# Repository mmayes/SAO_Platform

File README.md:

# SAP Display Platform

I had made this project after returning home from Def Con 30 with a brand 
new colelction of SAOs that jsut had to be displayed somehow.

## Fabrication

I had targeted JLCPCB.com as the manufacturer of this pcb to include their 
pick and place service. To that end the zipped gerber file along with 
the files contained within the fabrication folder were sufficient to 
facilaite that. It's quite possible that the LCSC Part number may have 
changed since then.

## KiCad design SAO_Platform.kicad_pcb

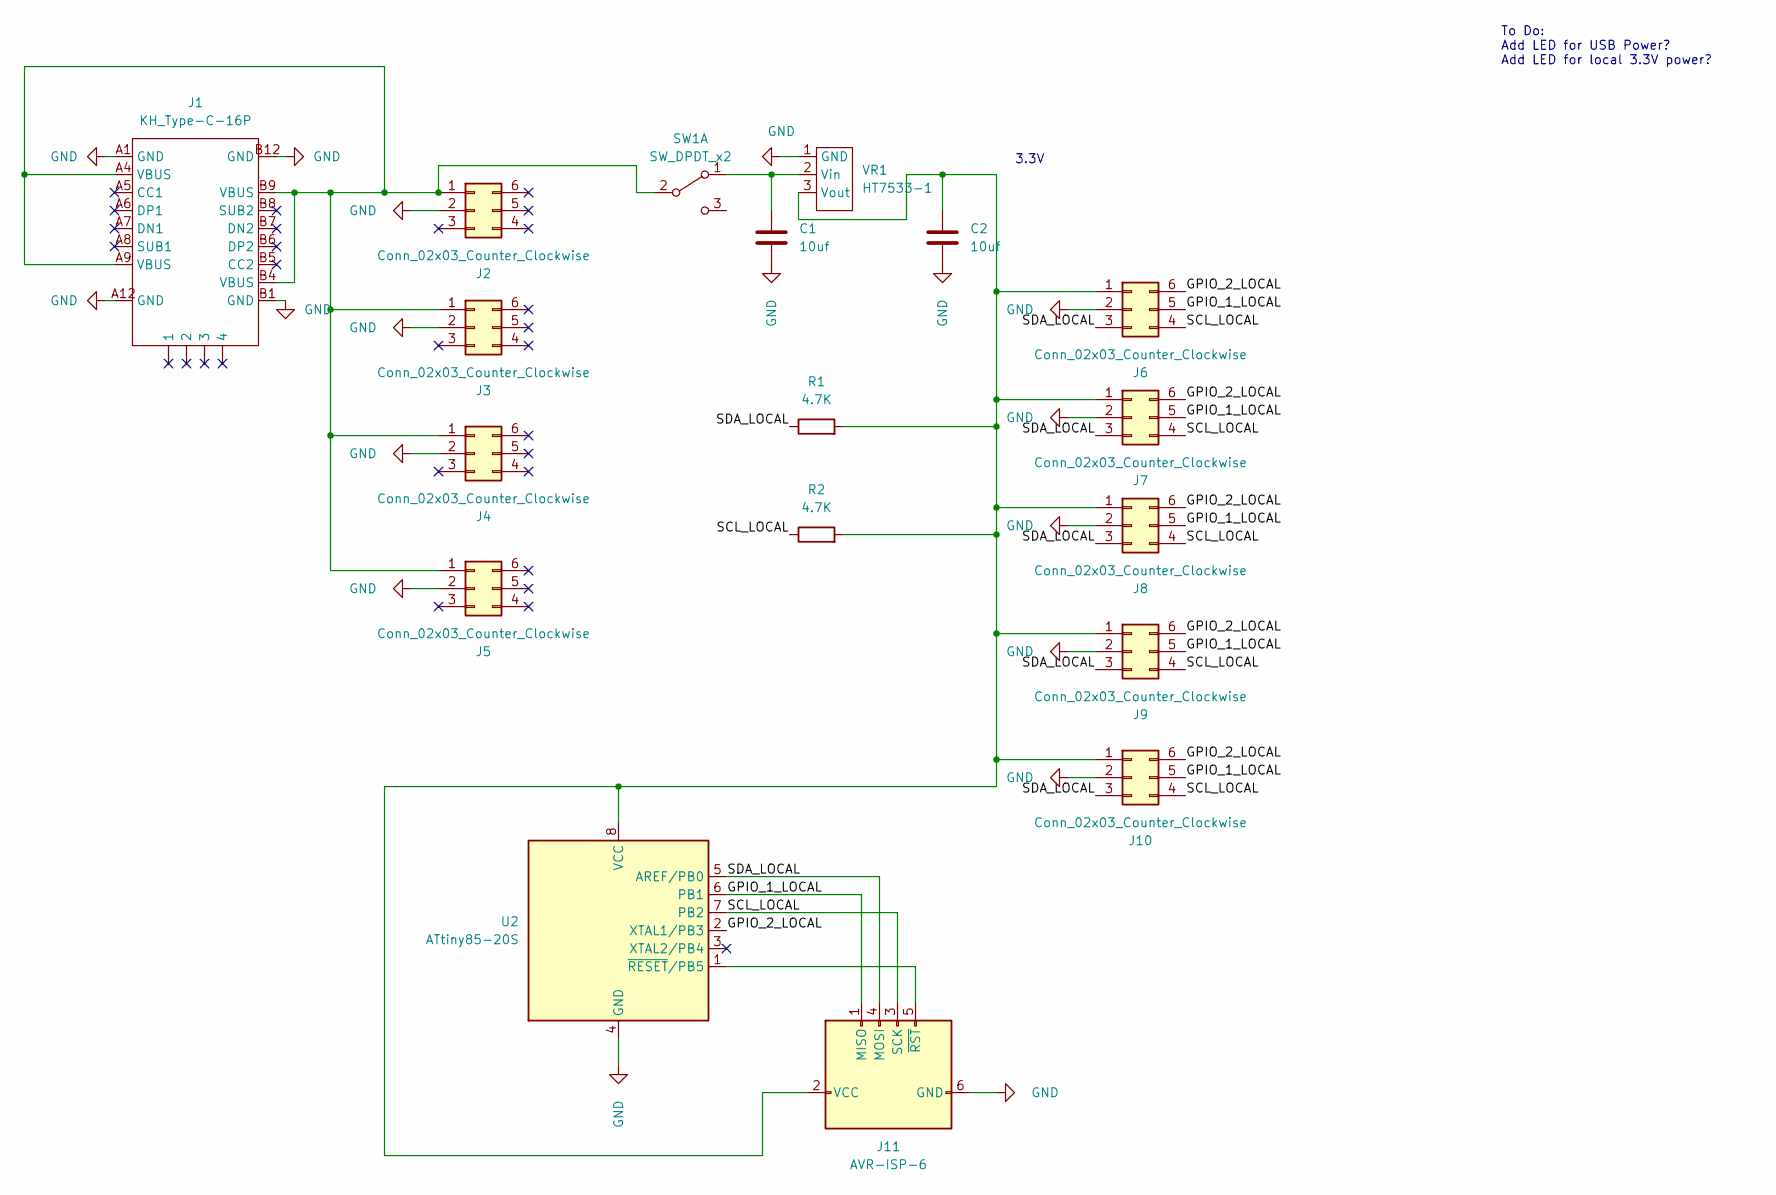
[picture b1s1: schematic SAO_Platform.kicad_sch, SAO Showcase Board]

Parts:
C1, C2: 10uf; C_0805_2012Metric
J1: KH_Type-C-16P; USB-C-SMD_KH-TYPE-C-16P
J2, J3, J4, J5, J6, J7, J8, J9, J10: Conn_02x03_Counter_Clockwise; PinSocket_2x03_P2.54mm_Vertical
J11: AVR-ISP-6
R1, R2: 4.7K; R_0805_2012Metric_Pad1.20x1.40mm_HandSolder
SW1: SW_DPDT_x2; switch_JS202011SCQN
U2: ATtiny85-20S; SOIC-8W_5.3x5.3mm_P1.27mm
VR1: HT7533-1; SOT-89-3

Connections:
/GPIO_1_LOCAL: J6.5, J7.5, J8.5, J9.5, J10.5, J11.1 (MISO), U2.6 (PB1)
/GPIO_2_LOCAL: J6.6, J7.6, J8.6, J9.6, J10.6, U2.2 (XTAL1/PB3)
/SCL_LOCAL: J6.4, J7.4, J8.4, J9.4, J10.4, J11.3 (SCK), R2.1, U2.7 (PB2)
/SDA_LOCAL: J6.3, J7.3, J8.3, J9.3, J10.3, J11.4 (MOSI), R1.1, U2.5 (AREF/PB0)
GND: C1.2, C2.2, J1.A1 (GND), J1.A12 (GND), J1.B1 (GND), J1.B12 (GND), J2.2, J3.2, J4.2, J5.2, J6.2, J7.2, J8.2, J9.2, J10.2, J11.6 (GND), U2.4 (GND), VR1.1 (GND)
unnamed: C1.1, SW1.1 (A), VR1.2 (Vin)
unnamed: C2.1, J6.1, J7.1, J8.1, J9.1, J10.1, J11.2 (VCC), R1.2, R2.2, U2.8 (VCC), VR1.3 (Vout)
unnamed: J1.A4 (VBUS), J1.A9 (VBUS), J1.B4 (VBUS), J1.B9 (VBUS), J2.1, J3.1, J4.1, J5.1, SW1.2 (B)
unnamed: J11.5 (~RST), U2.1 (~RESET/PB5)

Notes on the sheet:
To Do: Add LED for USB Power? Add LED for local 3.3V power?
3.3V

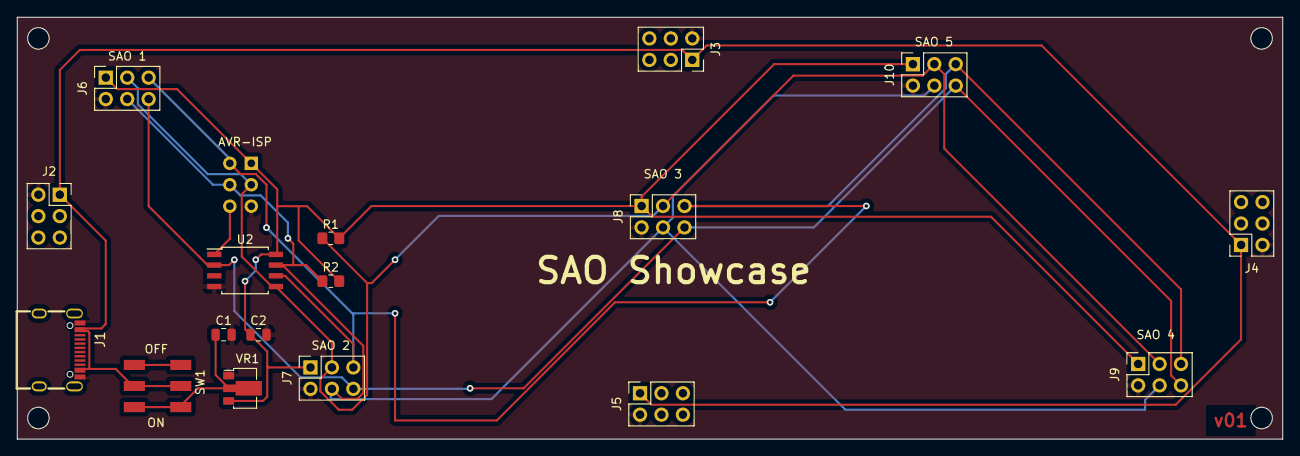
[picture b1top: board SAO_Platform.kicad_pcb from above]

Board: 2 copper layers, 150.0 x 50.0 mm, 19 parts (0 on the bottom side), 9 nets.

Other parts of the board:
svg2mod: G***; 26R

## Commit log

2023-02-20 readme updates
2023-02-20 include picture
2023-07-28 reference runway images for the SAO platform
